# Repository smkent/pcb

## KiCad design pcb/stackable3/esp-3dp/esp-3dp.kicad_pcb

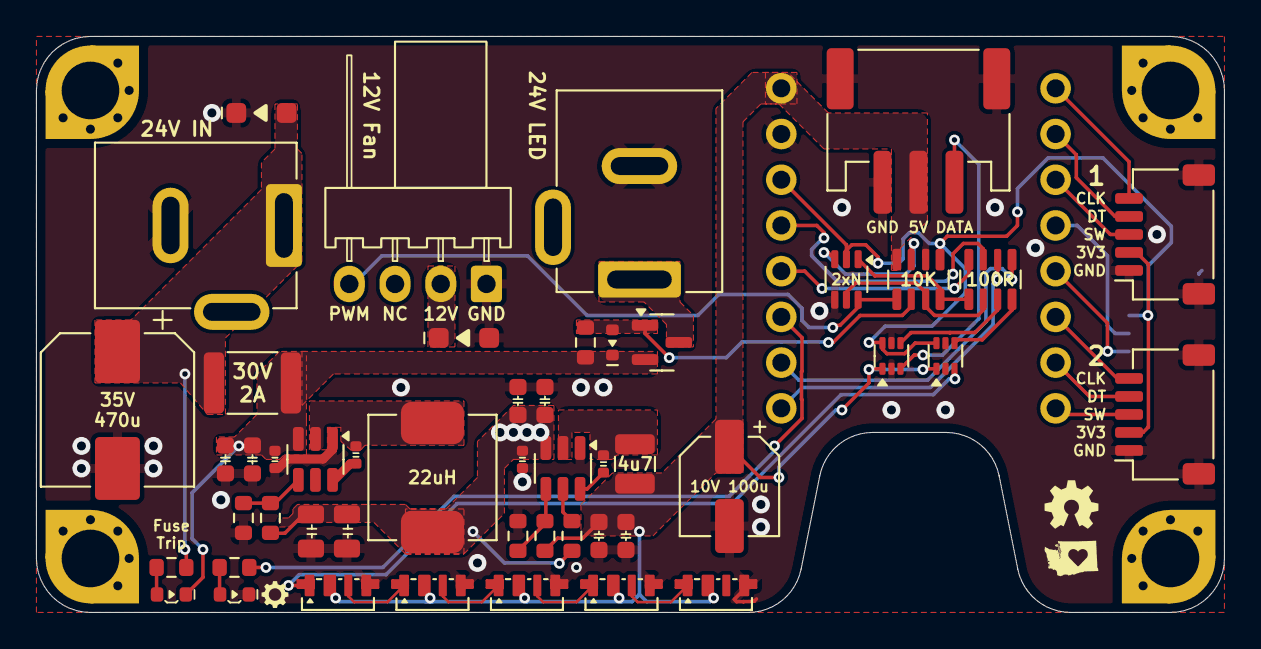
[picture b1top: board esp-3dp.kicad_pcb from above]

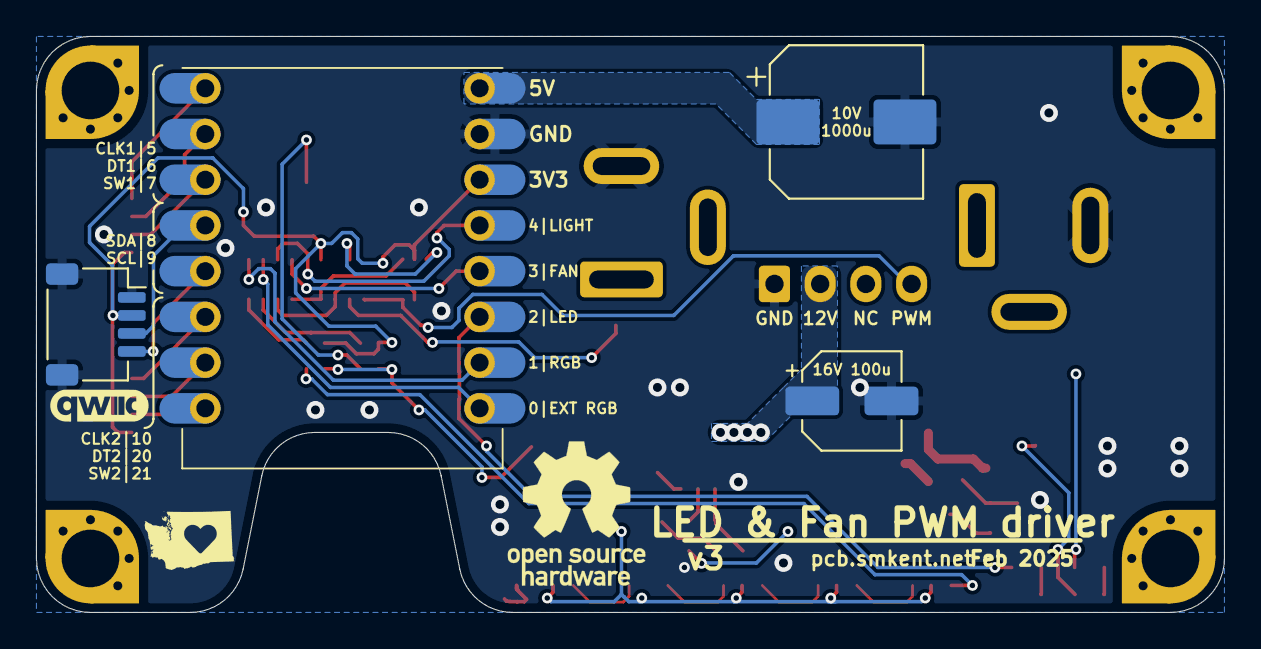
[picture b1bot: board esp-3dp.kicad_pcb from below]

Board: 2 copper layers, 66.0 x 32.0 mm, 53 parts (4 on the bottom side), 42 nets.

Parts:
C1, C2, C8, C9: 10u; C_0603_1608Metric
C3, C4, C10, C11: 0u1; C_0402_1005Metric
C5, C6: 22u; C_0805_2012Metric
C7: 470u; CP_Elec_8x10
C12, C13: 22u; C_0603_1608Metric
C14, C16: 100u; CP_Elec_5x5.4
C15: 1000u; CP_Elec_8x10
D1: DSK34W; D_SOD-123F
D2: D_TVS; D_SOD-123F
D3: 10V; D_SOD-523
F1: 30V 2A; Fuse_1812_4532Metric
J0, J1: DC-005; BarrelJack_DC-005_THT_Horizontal
J2, J3: JST SH; JST_SH_SM05B-SRSS-TB_1x05-1MP_P1.00mm_Horizontal
J4: STEMMA-Signal; STEMMA-Signal-SMD-horizontal
J5: Qwiic; Qwiic-SMD-horizontal
L1: 22u; L_Power_7.0x6.6mm_0630
L2: 4u7; L_1008_2520Metric
LED1: XL-1606UWC; LED_SideEmitter_1.7x1.1mm
LED2: XL-1606SURC; LED_SideEmitter_1.7x1.1mm
M1: KF2510; FanPinHeader_1x04_P2.54mm_Horizontal
PIX1, PIX2, PIX3, PIX4, PIX5: SK6812SIDE-A; LED_SK6812SIDE-A_4.0x1.6mm
Q1: 2N7002DW; SOT-363_SC-70-6_HandSolder
Q3: AO3401A; SOT-23
R0, R2: 5K1; R_0603_1608Metric
R1: 100K; R_0603_1608Metric
R3: 1K; R_0603_1608Metric
R4: 57K6; R_0603_1608Metric
R6, R7: 10K; R_0603_1608Metric
R12: 17K4; R_0603_1608Metric
RN1: 10K; R_Array_Convex_4x0603_HandSolder
RN2: 100R; R_Array_Convex_4x0603_HandSolder
SM1: ESP32-C3-Super-Mini-Castellated-SMD
U1: TPS54202DDCR; SOT-23-6
U2: TPS563201; SOT-23-6
U4, U5: SN74LVC1T45Z6; SOT-563

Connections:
+3V3: J2.2 (+3V3), J3.2 (+3V3), J5.2 (+3V3), Q1.2 (G), RN1.5 (R4.2), SM1.3V3 (+3.3V), U4.6 (VCCB), U5.6 (VCCB)
+5V: C12.1, C13.1, C14.1, C15.1, J4.2 (V+), L2.2, PIX1.2 (VDD), PIX2.2 (VDD), PIX3.2 (VDD), PIX4.2 (VDD), PIX5.2 (VDD), R4.2, RN1.8 (R1.2), SM1.5V (+5V), U4.1 (VCCA), U5.1 (VCCA)
+12V: C5.1, C6.1, C8.1, C9.1, C10.1, C16.1, D1.1 (K), L1.2, M1.2 (+), R1.2, R7.1, U2.3 (VIN)
+24V: C1.1, C2.1, C3.1, D3.1 (K), F1.2, LED2.1 (K), Q3.2 (S), R12.1, U1.3 (VIN)
/24V_IN_RAW: C7.1, D2.2 (A2), F1.1, J0.1, R3.2
/FAN_PWM_3V3_R: Q1.1 (S), RN1.4 (R4.1), RN2.1 (R1.1)
/NP_1_DATA_3V3_R: RN2.4 (R4.1), U4.4 (B)
/NP_2_DATA_3V3_R: RN2.3 (R3.1), U5.4 (B)
/N_DRAIN_1: Q1.3 (D), RN1.7 (R2.2)
/N_GATE_1: Q1.5 (G), RN1.3 (R3.1), RN2.2 (R2.1)
/PIX2_DATA_S: PIX1.3 (DOUT), PIX2.1 (DIN)
/PIX3_DATA_S: PIX2.3 (DOUT), PIX3.1 (DIN)
/PIX4_DATA_S: PIX3.3 (DOUT), PIX4.1 (DIN)
/PIX5_DATA_S: PIX4.3 (DOUT), PIX5.1 (DIN)
/P_GATE_1: D3.2 (A), Q3.1 (G), R12.2, RN1.2 (R2.1)
/SW_5V: C11.2, L2.1, U2.2 (SW)
/SW_12V: C4.2, L1.1, U1.2 (SW)
ENC1_BUTTON: J2.3 (SW), SM1.7 (GPIO7/SS)
ENC1_CLK: J2.5 (CLK), SM1.5 (GPIO5/MISO)
ENC1_DT: J2.4 (DT), SM1.6 (GPIO6/MOSI)
ENC2_BUTTON: J3.3 (SW), SM1.21 (GPIO21/TX)
ENC2_CLK: J3.5 (CLK), SM1.10 (GPIO10)
ENC2_DT: J3.4 (DT), SM1.20 (GPIO20/RX)
FAN_PWM_3V3: RN2.8 (R1.2), SM1.3 (ADC/GPIO3)
FAN_PWM_5V: M1.4 (PWM), Q1.6 (D), RN1.1 (R1.1)
FB_5V: R4.1, R6.2, U2.4 (VFB)
FB_12V: R1.1, R2.2, U1.4 (FB)
GND: C1.2, C2.2, C3.2, C5.2, C6.2, C7.2, C8.2, C9.2, C10.2, C12.2, C13.2, C14.2, C15.2, C16.2, D1.2 (A), D2.1 (A1), J0.2, J1.2, J2.1 (GND), J2.MP, J3.1 (GND), J3.MP, J4.3 (GND), J4.MP, J5.1 (GND), J5.MP, LED1.1 (K), M1.1 (-), PIX1.4 (VSS), PIX2.4 (VSS), PIX3.4 (VSS), PIX4.4 (VSS), PIX5.4 (VSS), Q1.4 (S), R2.1, R6.1, RN1.6 (R3.2), SM1.G (GND), U1.1 (GND), U2.1 (GND), U4.2 (GND), U4.5 (DIR), U5.2 (GND), U5.5 (DIR)
LIGHT_OUT: J1.1, Q3.3 (D)
LIGHT_PWM_3V3: RN2.7 (R2.2), SM1.4 (SCK/ADC/GPIO4)
NEOPIXEL_1_DATA_3V3: RN2.5 (R4.2), SM1.1 (ADC/GPIO1)
NEOPIXEL_1_DATA_5V: PIX1.1 (DIN), U4.3 (A)
NEOPIXEL_2_DATA_3V3: RN2.6 (R3.2), SM1.0 (ADC/GPIO0)
NEOPIXEL_2_DATA_5V: J4.1 (Sig), U5.3 (A)
unnamed: LED1.2 (A), R0.1
unnamed: LED2.2 (A), R3.1
unnamed: C4.1, U1.6 (BOOT)
unnamed: R7.2, U2.5 (EN)
unnamed: C11.1, U2.6 (VBST)
SCL: J5.4 (SCL), SM1.9 (~GPIO9/SCL)
SDA: J5.3 (SDA), SM1.8 (~GPIO8/SDA)
STATUS_LED: R0.2, SM1.2 (ADC/~GPIO2)

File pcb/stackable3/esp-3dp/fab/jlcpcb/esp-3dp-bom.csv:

Comment,Designator,Footprint,LCSC
0u1,"C3,C4,C10,C11",discrete:C_0402_1005Metric,
SN74LVC1T45Z6,"U4,U5",Package_TO_SOT_SMD:SOT-563,C441819
22u,L1,discrete:L_Power_7.0x6.6mm_0630,
SK6812SIDE-A,"PIX1,PIX2,PIX3,PIX4,PIX5",discrete:LED_SK6812SIDE-A_4.0x1.6mm,C2890037
TPS563201,U2,Package_TO_SOT_SMD:SOT-23-6,C116592
DC-005,"J0,J1",connector:BarrelJack_DC-005_THT_Horizontal,
22u,"C5,C6",discrete:C_0805_2012Metric,
~,SM1,module:ESP32-C3-Super-Mini-Castellated-SMD,
100u,"C14,C16",Capacitor_SMD:CP_Elec_5x5.4,C4054379
XL-1606SURC,LED2,discrete:LED_SideEmitter_1.7x1.1mm,C965860
5K1,"R0,R2",Resistor_SMD:R_0603_1608Metric,
4u7,L2,discrete:L_1008_2520Metric,C22471106
57K6,R4,Resistor_SMD:R_0603_1608Metric,C23082
10u,"C1,C2,C8,C9",discrete:C_0603_1608Metric,
Qwiic,J5,connector:Qwiic-SMD-horizontal,C19270571
17K4,R12,Resistor_SMD:R_0603_1608Metric,C22819
100R,RN2,discrete:R_Array_Convex_4x0603_HandSolder,C270393
2N7002DW,Q1,package:SOT-363_SC-70-6_HandSolder,C5190214
10K,RN1,discrete:R_Array_Convex_4x0603_HandSolder,C110924
30V 2A,F1,Fuse:Fuse_1812_4532Metric,C22366122
JST SH,"J2,J3",connector:JST_SH_SM05B-SRSS-TB_1x05-1MP_P1.00mm_Horizontal,C7433426
DSK34W,D1,package:D_SOD-123F,C3014041
470u,C7,Capacitor_SMD:CP_Elec_8x10,C7471889
100K,R1,Resistor_SMD:R_0603_1608Metric,
AO3401A,Q3,Package_TO_SOT_SMD:SOT-23,
10V,D3,package:D_SOD-523,C2832579
TPS54202DDCR,U1,Package_TO_SOT_SMD:SOT-23-6,C191884
1000u,C15,Capacitor_SMD:CP_Elec_8x10,C311227
22u,"C12,C13",discrete:C_0603_1608Metric,
D_TVS,D2,package:D_SOD-123F,C7473232
10K,"R6,R7",Resistor_SMD:R_0603_1608Metric,
KF2510,M1,connector:FanPinHeader_1x04_P2.54mm_Horizontal,
XL-1606UWC,LED1,discrete:LED_SideEmitter_1.7x1.1mm,C965866
STEMMA-Signal,J4,connector:STEMMA-Signal-SMD-horizontal,C5372880
1K,R3,Resistor_SMD:R_0603_1608Metric,

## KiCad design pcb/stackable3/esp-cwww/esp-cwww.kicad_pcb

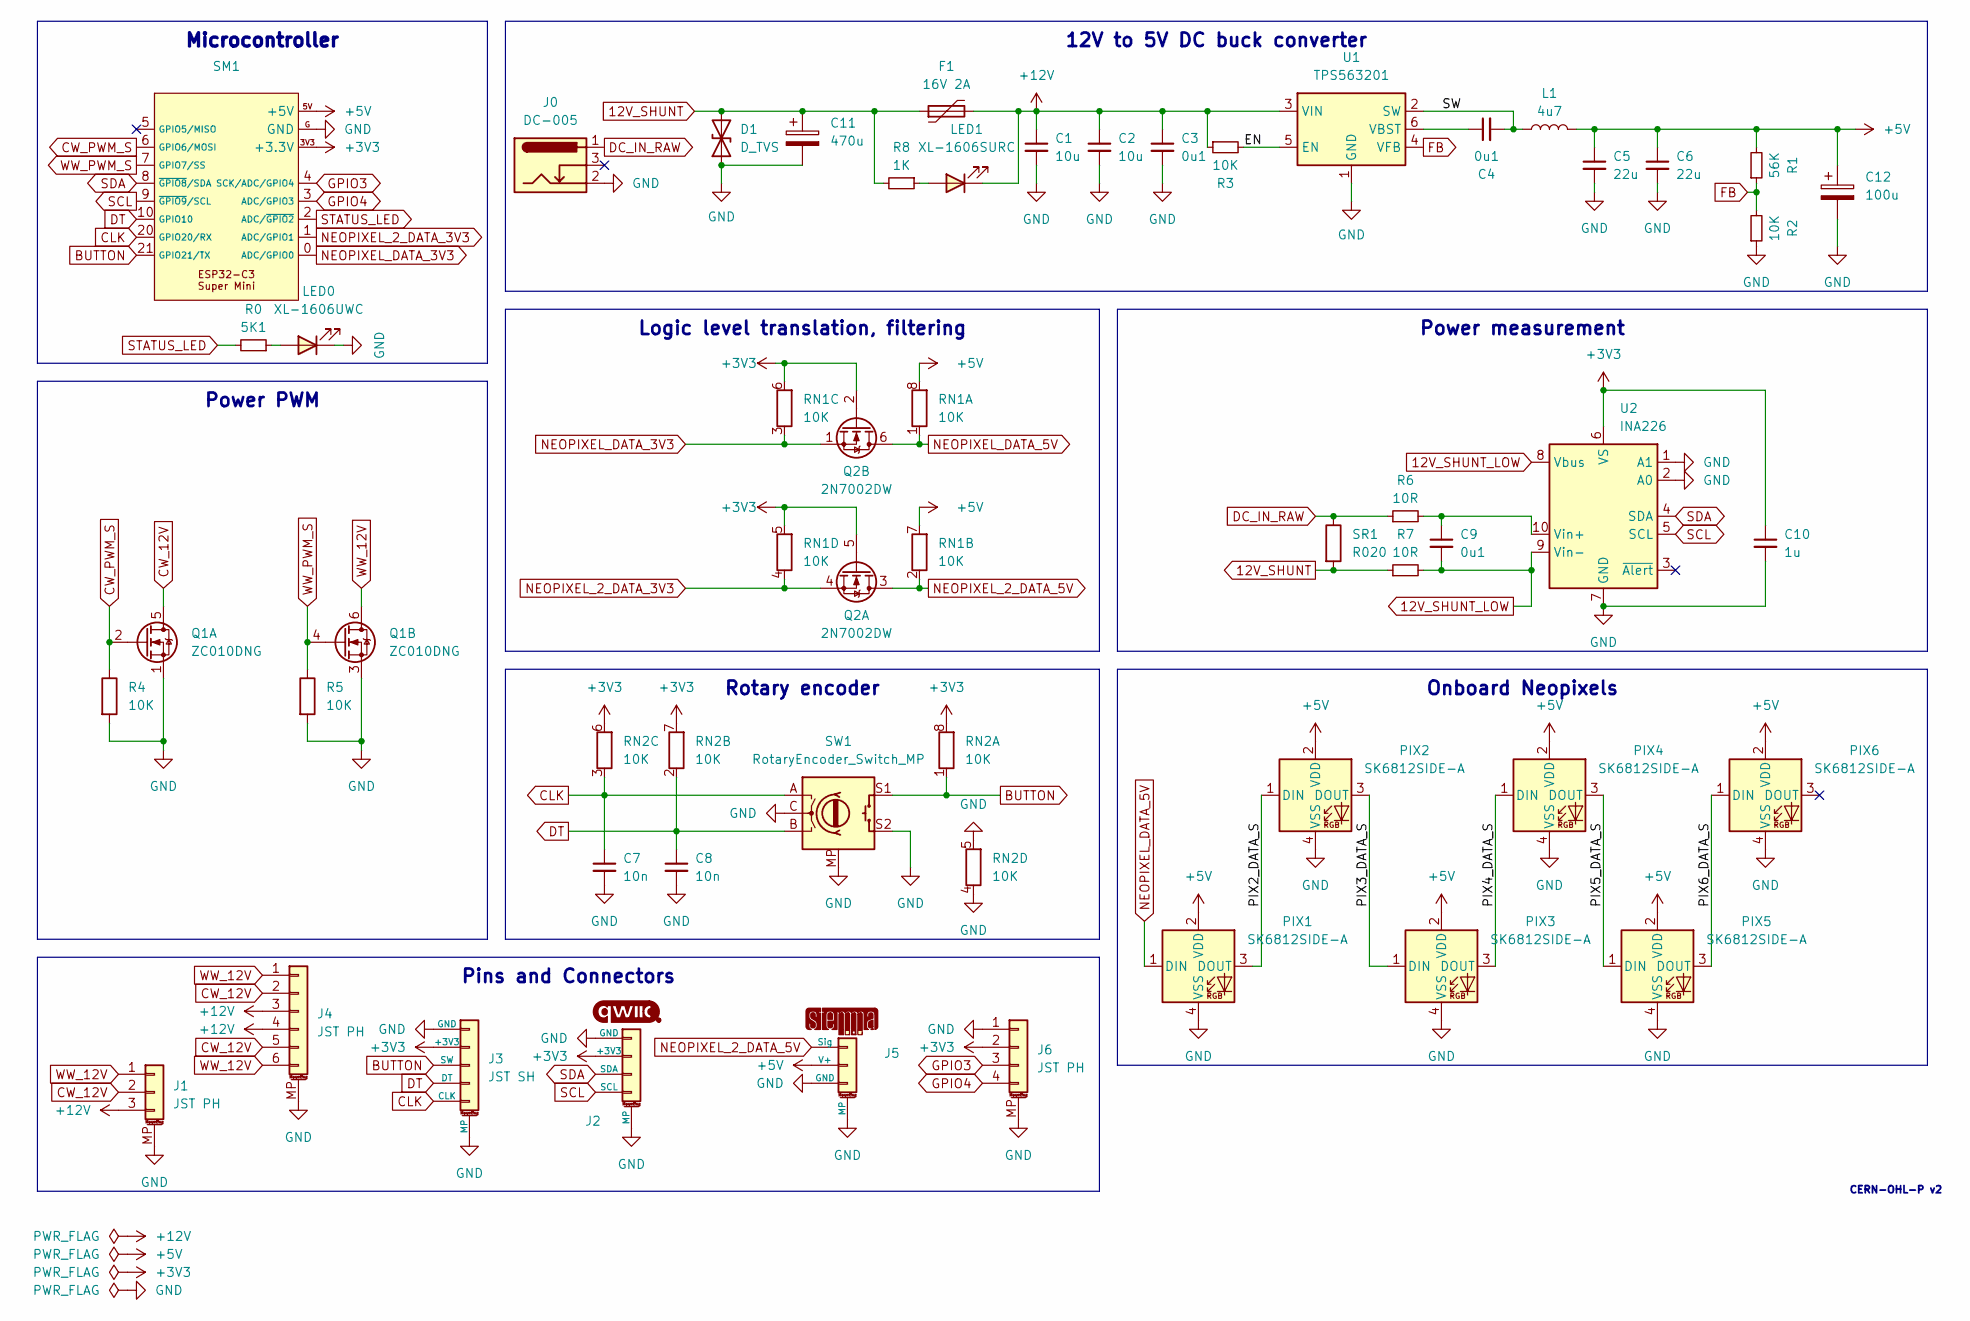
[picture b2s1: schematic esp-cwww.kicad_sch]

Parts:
C1, C2: 10u; C_0603_1608Metric
C3, C4: 0u1; C_0603_1608Metric
C5, C6: 22u; C_0603_1608Metric
C7, C8: 10n; C_0603_1608Metric
C9: 0u1; C_0402_1005Metric; LCSC Part C152814
C10: 1u; C_0402_1005Metric
C11: 470u; CP_Elec_8x10; LCSC Part C7471889
C12: 100u; CP_Elec_5x5.4; LCSC Part C4054379
D1: D_TVS; D_SOD-123F; LCSC Part C7473216
F1: 16V 2A; Fuse_1206_3216Metric; LCSC Part C2982271
J0: DC-005; BarrelJack_DC-005_THT_Horizontal
J1: JST PH; STEMMA-Signal-SMD-horizontal; LCSC Part C5372880
J2: Qwiic; Qwiic-SMD-horizontal-logo; LCSC Part C19270571
J3: JST SH; JST_SH_SM05B-SRSS-TB_1x05-1MP_P1.00mm_Horizontal; LCSC Part C7433426
J4: JST PH; JST_PH_S6B-PH-SM4-TB_1x06-1MP_P2.00mm_Horizontal; LCSC Part C7433652
J5: STEMMA-Signal; STEMMA-Signal-SMD-horizontal; LCSC Part C5372880
J6: JST PH; JST_PH_S4B-PH-SM4-TB_1x04-1MP_P2.00mm_Horizontal; LCSC Part C5343396
L1: 4u7; L_1008_2520Metric; LCSC Part C22471106
LED0: XL-1606UWC; LED_SideEmitter_1.7x1.1mm; LCSC Part C965866
LED1: XL-1606SURC; LED_SideEmitter_1.7x1.1mm; LCSC Part C965860
PIX1, PIX2, PIX3, PIX4, PIX5, PIX6: SK6812SIDE-A; LED_SK6812SIDE-A_4.0x1.6mm; LCSC Part C2890037
Q1: ZC010DNG; PDFN-8_L3.2-W3.1-P0.65-LS3.4-BL-EP2; LCSC Part C36499170
Q2: 2N7002DW; SOT-363_SC-70-6_HandSolder; LCSC Part C5190214
R0: 5K1; R_0603_1608Metric
R1: 56K; R_0603_1608Metric
R2, R3: 10K; R_0603_1608Metric
R4, R5: 10K; R_0402_1005Metric
R6, R7: 10R; R_0402_1005Metric; LCSC Part C25077
R8: 1K; R_0603_1608Metric
RN1, RN2: 10K; R_Array_Convex_4x0603_HandSolder; LCSC Part C110924
SM1: ESP32-C3-Super-Mini-Castellated-SMD
SR1: R020; R_2512_6332Metric_Pad1.40x3.35mm_HandSolder; LCSC Part C5375467
SW1: RotaryEncoder_Switch_MP; RotaryEncoder_Alps_EC11-Switch_Horizontal_H20mm
U1: TPS563201; SOT-23-6; LCSC Part C116592
U2: INA226; VSSOP-10_3x3mm_P0.5mm; LCSC Part C49851

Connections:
12V_SHUNT: C11.1, D1.2 (A2), F1.1, R7.1, R8.2, SR1.2
12V_SHUNT_LOW: C9.2, R7.2, U2.8 (Vbus), U2.9 (Vin-)
+3V3: C10.1, J2.2 (+3V3), J3.2 (+3V3), J6.2, Q2.2 (G), Q2.5 (G), RN1.5 (R4.2), RN1.6 (R3.2), RN2.6 (R3.2), RN2.7 (R2.2), RN2.8 (R1.2), SM1.3V3 (+3.3V), U2.6 (VS)
+5V: C5.1, C6.1, C12.1, J5.2 (V+), L1.2, PIX1.2 (VDD), PIX2.2 (VDD), PIX3.2 (VDD), PIX4.2 (VDD), PIX5.2 (VDD), PIX6.2 (VDD), R1.2, RN1.7 (R2.2), RN1.8 (R1.2), SM1.5V (+5V)
+12V: C1.1, C2.1, C3.1, F1.2, J1.3, J4.3, J4.4, LED1.1 (K), R3.1, U1.3 (VIN)
/EN: R3.2, U1.5 (EN)
/PIX2_DATA_S: PIX1.3 (DOUT), PIX2.1 (DIN)
/PIX3_DATA_S: PIX2.3 (DOUT), PIX3.1 (DIN)
/PIX4_DATA_S: PIX3.3 (DOUT), PIX4.1 (DIN)
/PIX5_DATA_S: PIX4.3 (DOUT), PIX5.1 (DIN)
/PIX6_DATA_S: PIX5.3 (DOUT), PIX6.1 (DIN)
/SW: C4.2, L1.1, U1.2 (SW)
BUTTON: J3.3 (SW), RN2.1 (R1.1), SM1.21 (GPIO21/TX), SW1.S1
CLK: C7.1, J3.5 (CLK), RN2.3 (R3.1), SM1.20 (GPIO20/RX), SW1.A
CW_12V: J1.2, J4.2, J4.5, Q1.5 (D)
CW_PWM_S: Q1.2 (G), R4.1, SM1.6 (GPIO6/MOSI)
DC_IN_RAW: J0.1, R6.1, SR1.1
DT: C8.1, J3.4 (DT), RN2.2 (R2.1), SM1.10 (GPIO10), SW1.B
FB: R1.1, R2.2, U1.4 (VFB)
GND: C1.2, C2.2, C3.2, C5.2, C6.2, C7.2, C8.2, C10.2, C11.2, C12.2, D1.1 (A1), J0.2, J1.MP (MountPin), J2.1 (GND), J2.MP, J3.1 (GND), J3.MP, J4.MP (MountPin), J5.3 (GND), J5.MP, J6.1, J6.MP (MountPin), LED0.1 (K), PIX1.4 (VSS), PIX2.4 (VSS), PIX3.4 (VSS), PIX4.4 (VSS), PIX5.4 (VSS), PIX6.4 (VSS), Q1.1 (S), Q1.3 (S), R2.1, R4.2, R5.2, RN2.4 (R4.1), RN2.5 (R4.2), SM1.G (GND), SW1.C, SW1.MP, SW1.S2, U1.1 (GND), U2.1 (A1), U2.2 (A0), U2.7 (GND)
GPIO3: J6.3, SM1.4 (SCK/ADC/GPIO4)
GPIO4: J6.4, SM1.3 (ADC/GPIO3)
NEOPIXEL_2_DATA_3V3: Q2.4 (S), RN1.4 (R4.1), SM1.1 (ADC/GPIO1)
NEOPIXEL_2_DATA_5V: J5.1 (Sig), Q2.3 (D), RN1.2 (R2.1)
NEOPIXEL_DATA_3V3: Q2.1 (S), RN1.3 (R3.1), SM1.0 (ADC/GPIO0)
NEOPIXEL_DATA_5V: PIX1.1 (DIN), Q2.6 (D), RN1.1 (R1.1)
unnamed: LED0.2 (A), R0.1
unnamed: LED1.2 (A), R8.1
unnamed: C4.1, U1.6 (VBST)
unnamed: C9.1, R6.2, U2.10 (Vin+)
SCL: J2.4 (SCL), SM1.9 (~GPIO9/SCL), U2.5 (SCL)
SDA: J2.3 (SDA), SM1.8 (~GPIO8/SDA), U2.4 (SDA)
STATUS_LED: R0.2, SM1.2 (ADC/~GPIO2)
WW_12V: J1.1, J4.1, J4.6, Q1.6 (D)
WW_PWM_S: Q1.4 (G), R5.1, SM1.7 (GPIO7/SS)

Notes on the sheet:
Onboard Neopixels
Logic level translation, filtering
Pins and Connectors
Power PWM
Power measurement
Rotary encoder
Microcontroller
12V to 5V DC buck converter
CERN-OHL-P v2

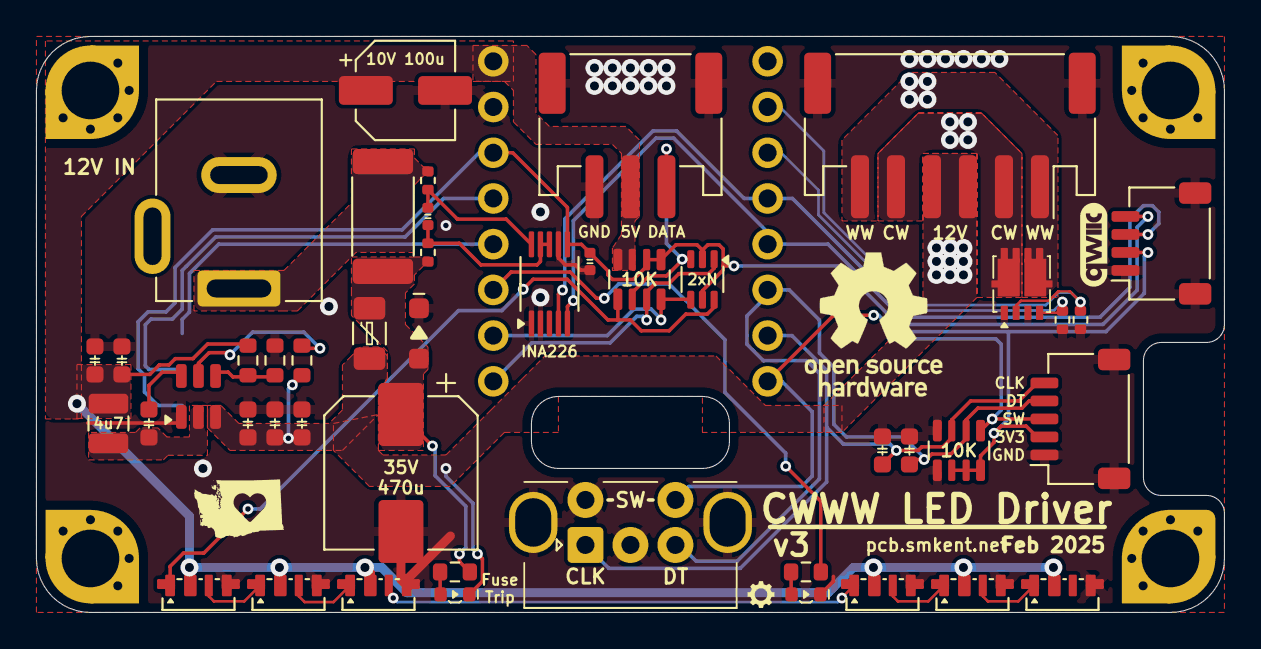
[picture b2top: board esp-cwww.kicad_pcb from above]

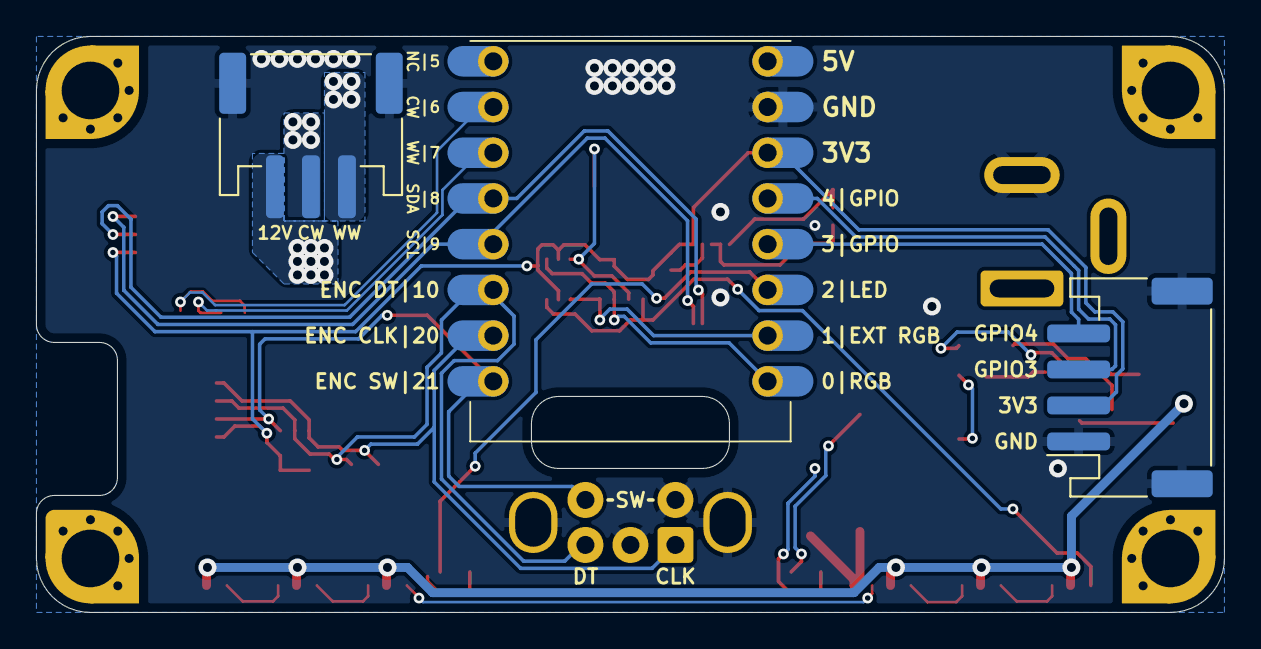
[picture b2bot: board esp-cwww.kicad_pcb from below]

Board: 2 copper layers, 66.0 x 32.0 mm, 48 parts (3 on the bottom side), 35 nets.

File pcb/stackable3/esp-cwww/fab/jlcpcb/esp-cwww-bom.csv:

Comment,Designator,Footprint,LCSC
STEMMA-Signal,J5,connector:STEMMA-Signal-SMD-horizontal,C5372880
100u,C12,Capacitor_SMD:CP_Elec_5x5.4,C4054379
XL-1606UWC,LED0,discrete:LED_SideEmitter_1.7x1.1mm,C965866
D_TVS,D1,package:D_SOD-123F,C7473216
JST SH,J3,connector:JST_SH_SM05B-SRSS-TB_1x05-1MP_P1.00mm_Horizontal,C7433426
~,SM1,module:ESP32-C3-Super-Mini-Castellated-SMD,
2N7002DW,Q2,package:SOT-363_SC-70-6_HandSolder,C5190214
SK6812SIDE-A,"PIX1,PIX2,PIX3,PIX4,PIX5,PIX6",discrete:LED_SK6812SIDE-A_4.0x1.6mm,C2890037
57K6,R1,Resistor_SMD:R_0603_1608Metric,C23082
0u1,"C3,C4",discrete:C_0603_1608Metric,
5K1,R0,Resistor_SMD:R_0603_1608Metric,
10K,"RN1,RN2",discrete:R_Array_Convex_4x0603_HandSolder,C110924
0u1,C9,discrete:C_0402_1005Metric,C152814
10u,"C1,C2",discrete:C_0603_1608Metric,
16V 2A,F1,discrete:Fuse_1206_3216Metric,C2982271
DC-005,J0,connector:BarrelJack_DC-005_THT_Horizontal,
22u,"C5,C6",discrete:C_0603_1608Metric,
10n,"C7,C8",discrete:C_0603_1608Metric,
Qwiic,J2,connector:Qwiic-SMD-horizontal-logo,C19270571
INA226,U2,Package_SO:VSSOP-10_3x3mm_P0.5mm,C49851
10R,"R6,R7",Resistor_SMD:R_0402_1005Metric,C25077
4u7,L1,discrete:L_1008_2520Metric,C22471106
XL-1606SURC,LED1,discrete:LED_SideEmitter_1.7x1.1mm,C965860
R020,SR1,Resistor_SMD:R_2512_6332Metric_Pad1.40x3.35mm_HandSolder,C5375467
470u,C11,Capacitor_SMD:CP_Elec_8x10,C7471889
JST PH,J1,connector:STEMMA-Signal-SMD-horizontal,C5372880
1K,R8,Resistor_SMD:R_0603_1608Metric,
ZC010DNG,Q1,package:PDFN-8_L3.2-W3.1-P0.65-LS3.4-BL-EP2,C36499170
10K,"R4,R5",Resistor_SMD:R_0402_1005Metric,
10K,"R2,R3",Resistor_SMD:R_0603_1608Metric,
JST PH,J6,connector:JST_PH_S4B-PH-SM4-TB_1x04-1MP_P2.00mm_Horizontal,C5343396
JST PH,J4,connector:JST_PH_S6B-PH-SM4-TB_1x06-1MP_P2.00mm_Horizontal,C7433652
RotaryEncoder_Switch_MP,SW1,electromechanical:RotaryEncoder_Alps_EC11-Switch_Horizontal_H20mm,
TPS563201,U1,package:SOT-23-6,C116592
1u,C10,discrete:C_0402_1005Metric,

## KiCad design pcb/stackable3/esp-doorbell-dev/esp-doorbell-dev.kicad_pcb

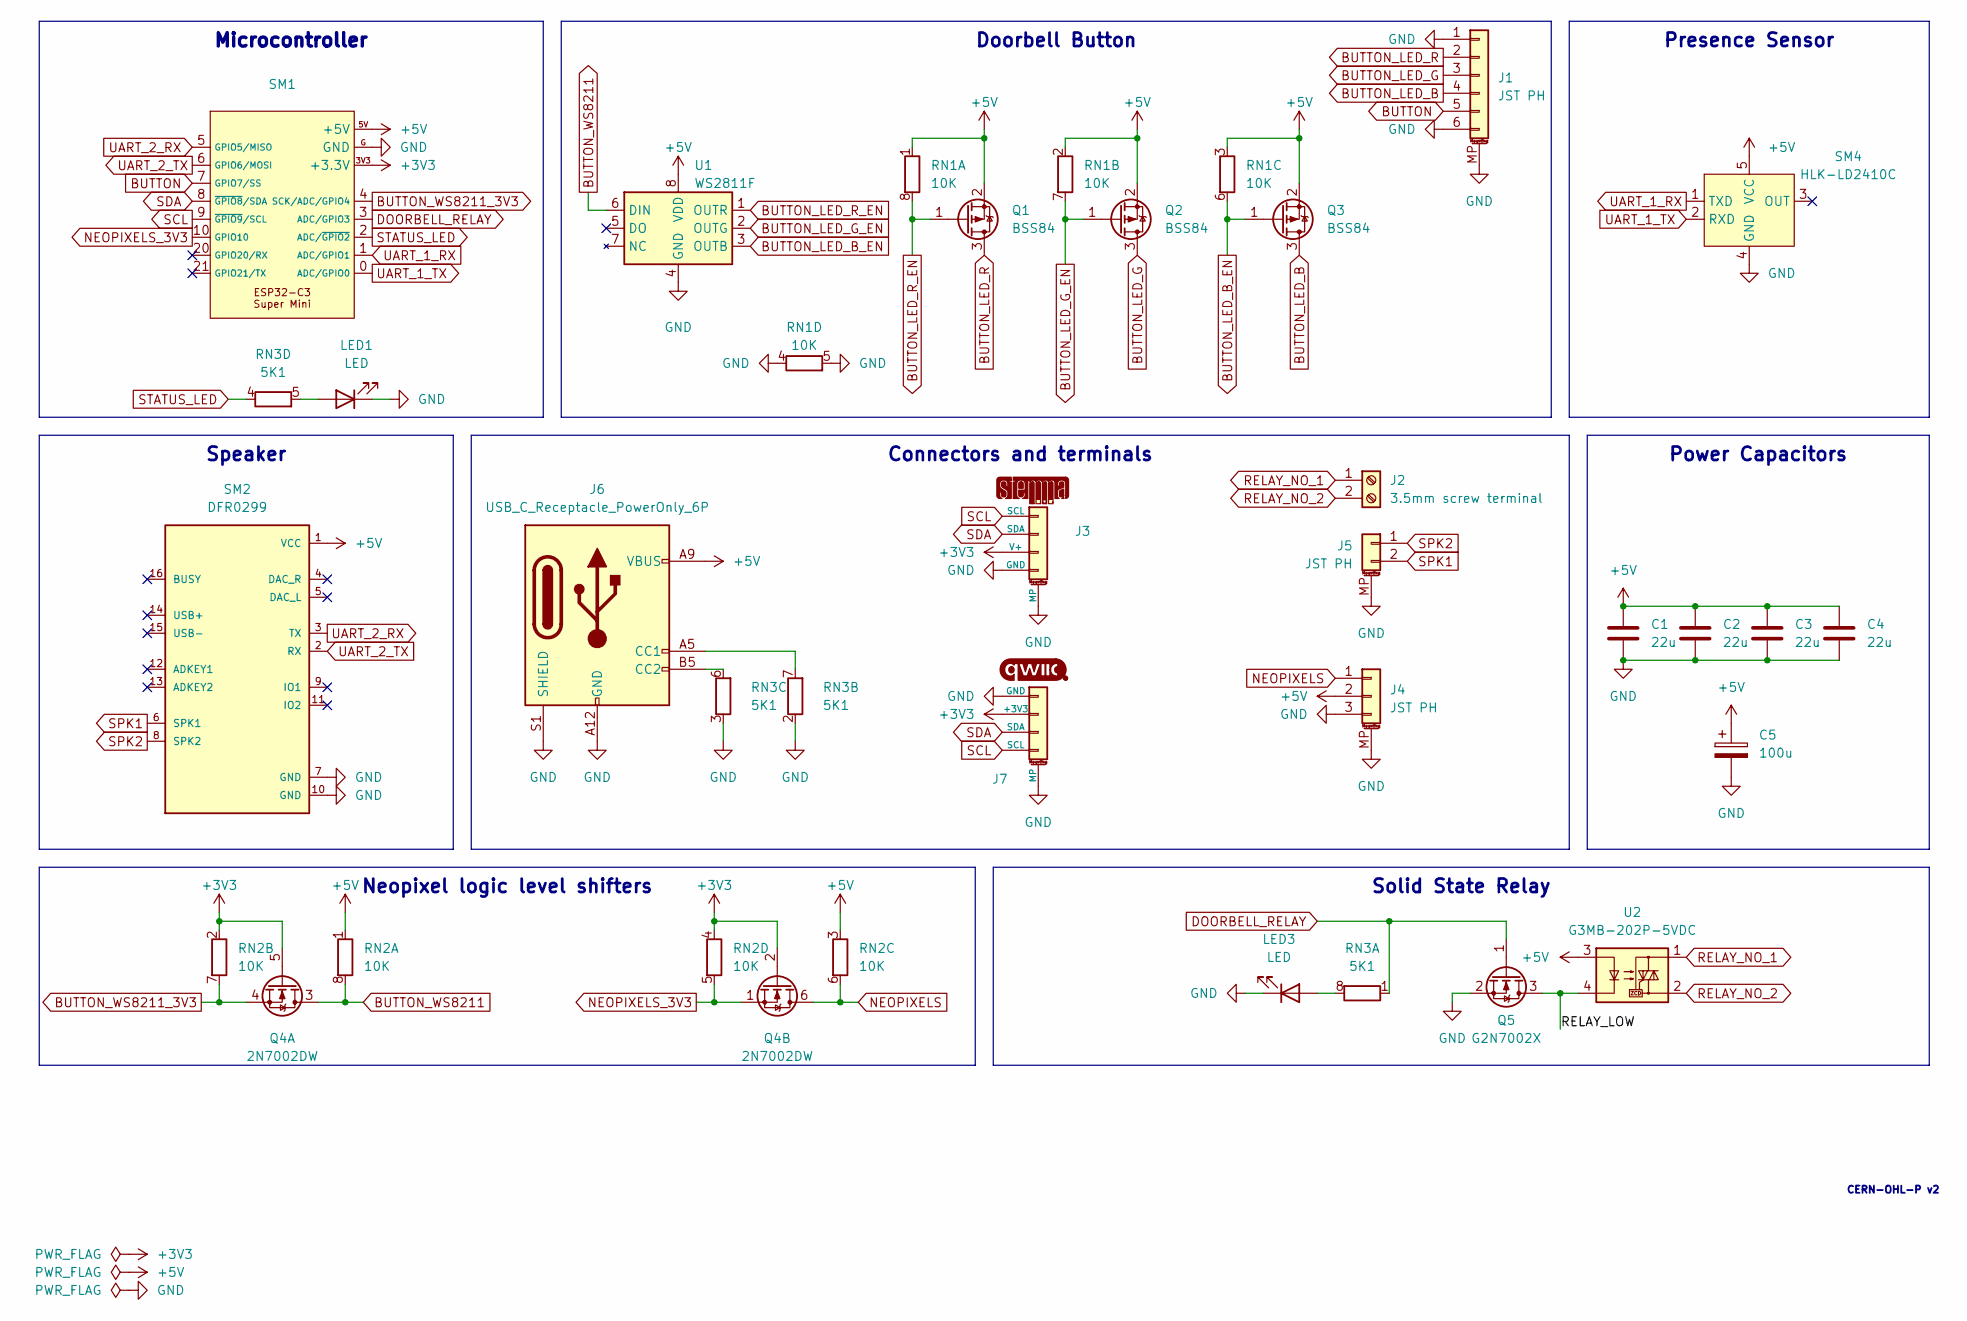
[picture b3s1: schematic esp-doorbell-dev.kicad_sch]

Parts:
C1, C2, C3, C4: 22u; C_0603_1608Metric
C5: 100u; CP_Elec_5x5.4; LCSC Part C4054379
J1: JST PH; JST_PH_S6B-PH-SM4-TB_1x06-1MP_P2.00mm_Horizontal
J2: 3.5mm screw terminal; TerminalBlock_Phoenix_PT-1,5-2-3.5-H_1x02_P3.50mm_Horizontal
J3: STEMMA; STEMMA-I2C-SMD-horizontal
J4: JST PH; STEMMA-Signal-SMD-horizontal
J5: JST PH; JST_PH_S2B-PH-SM4-TB_1x02-1MP_P2.00mm_Horizontal
J6: USB_C_Receptacle_PowerOnly_6P; USB_C_Receptacle_GCT_USB4125-xx-x_6P_TopMnt_Horizontal_Hand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; LCSC Part C2927029
J7: Qwiic; Qwiic-SMD-horizontal-logo; LCSC Part C19270571
LED1, LED3: LED; LED_0603_1608Metric_Pad1.05x0.95mm_HandSolder_simple
Q1, Q2, Q3: BSS84; SOT-23
Q4: 2N7002DW; SOT-363_SC-70-6_HandSolder; LCSC Part C5190214
Q5: G2N7002X; SOT-523; LCSC Part C5258971
RN1, RN2: 10K; R_Array_Convex_4x0603_HandSolder
RN3: 5K1; R_Array_Convex_4x0603_HandSolder
SM1: ESP32-C3-Super-Mini-Pins
SM2: DFR0299; DFPlayer-Mini-DFR0299-module
SM4: HLK-LD2410C; HLK-LD2410C-module; LCSC Part C19723500
U1: WS2811F; FSOP-8_3.3x1.7mm_P0.80mm; LCSC Part C5446692
U2: G3MB-202P-5VDC; Relay_G3MB-202P

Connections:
+3V3: J3.3 (V+), J7.2 (+3V3), Q4.2 (G), Q4.5 (G), RN2.2 (R2.1), RN2.4 (R4.1), SM1.3V3 (+3.3V)
+5V: C1.1, C2.1, C3.1, C4.1, C5.1, J4.2, J6.A9 (VBUS), J6.B9 (VBUS), Q1.2 (S), Q2.2 (S), Q3.2 (S), RN1.1 (R1.1), RN1.2 (R2.1), RN1.3 (R3.1), RN2.1 (R1.1), RN2.3 (R3.1), SM1.5V (+5V), SM2.1 (VCC), SM4.5 (VCC), U1.8 (VDD), U2.3
/RELAY_LOW: Q5.3 (D), U2.4
BUTTON: J1.5, SM1.7 (GPIO7/SS)
BUTTON_LED_B: J1.4, Q3.3 (D)
BUTTON_LED_B_EN: Q3.1 (G), RN1.6 (R3.2), U1.3 (OUTB)
BUTTON_LED_G: J1.3, Q2.3 (D)
BUTTON_LED_G_EN: Q2.1 (G), RN1.7 (R2.2), U1.2 (OUTG)
BUTTON_LED_R: J1.2, Q1.3 (D)
BUTTON_LED_R_EN: Q1.1 (G), RN1.8 (R1.2), U1.1 (OUTR)
BUTTON_WS8211: Q4.3 (D), RN2.8 (R1.2), U1.6 (DIN)
BUTTON_WS8211_3V3: Q4.4 (S), RN2.7 (R2.2), SM1.4 (SCK/ADC/GPIO4)
DOORBELL_RELAY: Q5.1 (G), RN3.1 (R1.1), SM1.3 (ADC/GPIO3)
GND: C1.2, C2.2, C3.2, C4.2, C5.2, J1.1, J1.6, J1.MP (MountPin), J3.4 (GND), J3.MP, J4.3, J4.MP (MountPin), J5.MP (MountPin), J6.A12 (GND), J6.B12 (GND), J6.S1 (SHIELD), J7.1 (GND), J7.MP, LED1.1 (K), LED3.1 (K), Q5.2 (S), RN1.4 (R4.1), RN1.5 (R4.2), RN3.2 (R2.1), RN3.3 (R3.1), SM1.G (GND), SM2.7 (GND), SM2.10 (GND), SM4.4 (GND), U1.4 (GND)
NEOPIXELS: J4.1, Q4.6 (D), RN2.6 (R3.2)
NEOPIXELS_3V3: Q4.1 (S), RN2.5 (R4.2), SM1.10 (GPIO10)
unnamed: J6.A5 (CC1), RN3.7 (R2.2)
unnamed: J6.B5 (CC2), RN3.6 (R3.2)
unnamed: LED1.2 (A), RN3.5 (R4.2)
unnamed: LED3.2 (A), RN3.8 (R1.2)
RELAY_NO_1: J2.1, U2.1
RELAY_NO_2: J2.2, U2.2
SCL: J3.1 (SCL), J7.4 (SCL), SM1.9 (~GPIO9/SCL)
SDA: J3.2 (SDA), J7.3 (SDA), SM1.8 (~GPIO8/SDA)
SPK1: J5.2, SM2.6 (SPK1)
SPK2: J5.1, SM2.8 (SPK2)
STATUS_LED: RN3.4 (R4.1), SM1.2 (ADC/~GPIO2)
UART_1_RX: SM1.1 (ADC/GPIO1), SM4.1 (TXD)
UART_1_TX: SM1.0 (ADC/GPIO0), SM4.2 (RXD)
UART_2_RX: SM1.5 (GPIO5/MISO), SM2.3 (TX)
UART_2_TX: SM1.6 (GPIO6/MOSI), SM2.2 (RX)

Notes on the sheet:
Microcontroller
Doorbell Button
Presence Sensor
Power Capacitors
Solid State Relay
Speaker
Neopixel logic level shifters
Connectors and terminals
CERN-OHL-P v2

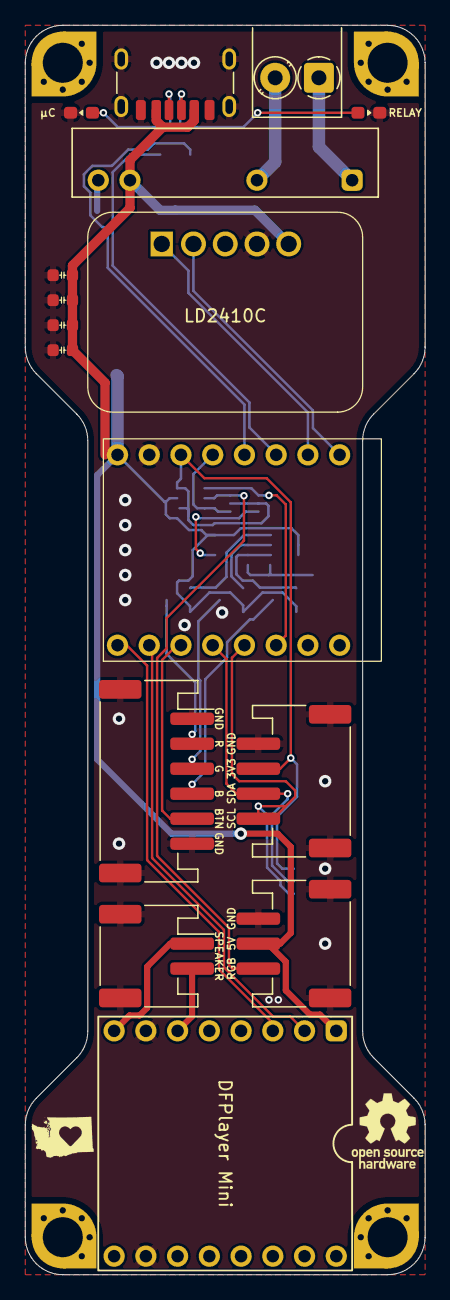
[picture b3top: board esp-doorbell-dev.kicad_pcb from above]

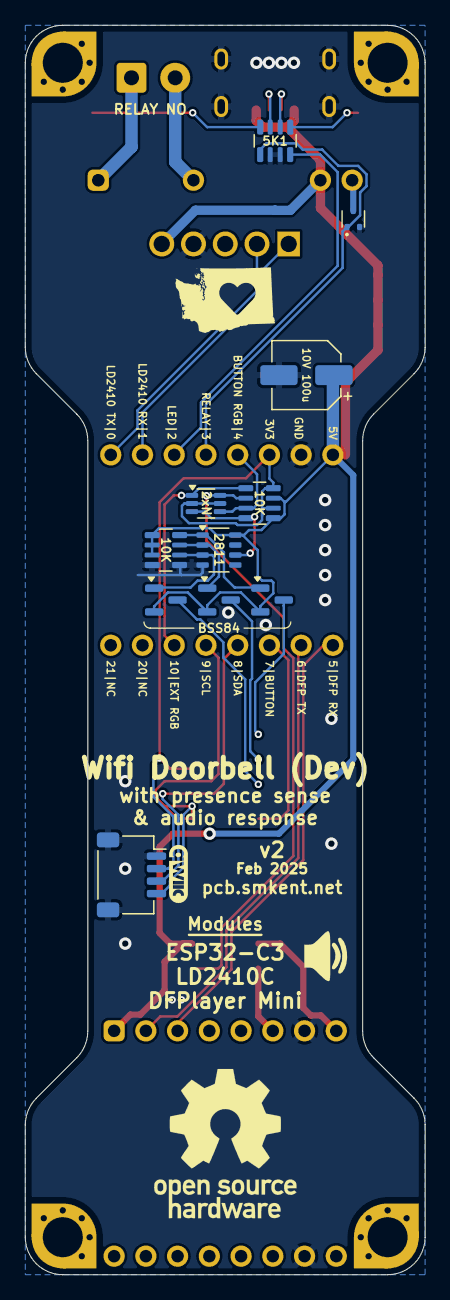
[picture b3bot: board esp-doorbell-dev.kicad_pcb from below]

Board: 2 copper layers, 32.0 x 100.0 mm, 27 parts (11 on the bottom side), 31 nets.

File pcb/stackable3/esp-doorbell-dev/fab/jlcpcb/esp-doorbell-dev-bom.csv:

Comment,Designator,Footprint,LCSC
22u,"C1,C2,C3,C4",discrete:C_0603_1608Metric,
BSS84,"Q1,Q2,Q3",package:SOT-23,
5K1,RN3,discrete:R_Array_Convex_4x0603_HandSolder,
G3MB-202P-5VDC,U2,discrete:Relay_G3MB-202P,
10K,"RN1,RN2",discrete:R_Array_Convex_4x0603_HandSolder,
100u,C5,Capacitor_SMD:CP_Elec_5x5.4,C4054379
Qwiic,J7,connector:Qwiic-SMD-horizontal-logo,C19270571
USB_C_Receptacle_PowerOnly_6P,J6,connector:USB_C_Receptacle_GCT_USB4125-xx-x_6P_TopMnt_Horizontal_HandSolder,C2927029
DFR0299,SM2,module:DFPlayer-Mini-DFR0299-module,
2N7002DW,Q4,package:SOT-363_SC-70-6_HandSolder,C5190214
G2N7002X,Q5,package:SOT-523,C5258971
HLK-LD2410C,SM4,module:HLK-LD2410C-module,C19723500
LED,"LED1,LED3",custom:LED_0603_1608Metric_Pad1.05x0.95mm_HandSolder_simple,
JST PH,J4,connector:STEMMA-Signal-SMD-horizontal,
STEMMA,J3,connector:STEMMA-I2C-SMD-horizontal,
3.5mm screw terminal,J2,"connector:TerminalBlock_Phoenix_PT-1,5-2-3.5-H_1x02_P3.50mm_Horizontal",
WS2811F,U1,package:FSOP-8_3.3x1.7mm_P0.80mm,C5446692
JST PH,J1,connector:JST_PH_S6B-PH-SM4-TB_1x06-1MP_P2.00mm_Horizontal,
JST PH,J5,connector:JST_PH_S2B-PH-SM4-TB_1x02-1MP_P2.00mm_Horizontal,
~,SM1,module:ESP32-C3-Super-Mini-Pins,
